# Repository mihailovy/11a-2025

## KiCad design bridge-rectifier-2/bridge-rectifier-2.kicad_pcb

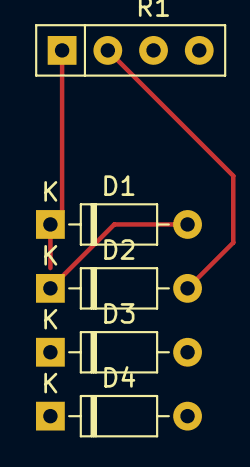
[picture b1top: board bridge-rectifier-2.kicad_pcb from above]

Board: 2 copper layers, 5 parts (0 on the bottom side), 4 nets.

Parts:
D1, D2, D3, D4: 1N4148; D_DO-35_SOD27_P7.62mm_Horizontal
R1: R; R_Array_SIP4

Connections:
unnamed: D1.2 (A), D2.1 (K)
unnamed: D1.1 (K), D3.1 (K), R1.1
unnamed: D2.2 (A), D4.2 (A), R1.2
unnamed: D3.2 (A), D4.1 (K)

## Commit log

2025-02-11 Add a KiCad Bridge Rectifer Project
